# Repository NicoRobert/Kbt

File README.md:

# Keyboard Turbo

This is my first attempt of designing a split keyboard.
Mainly inspired by the [event0]( https://github.com/devplayer0/event0)

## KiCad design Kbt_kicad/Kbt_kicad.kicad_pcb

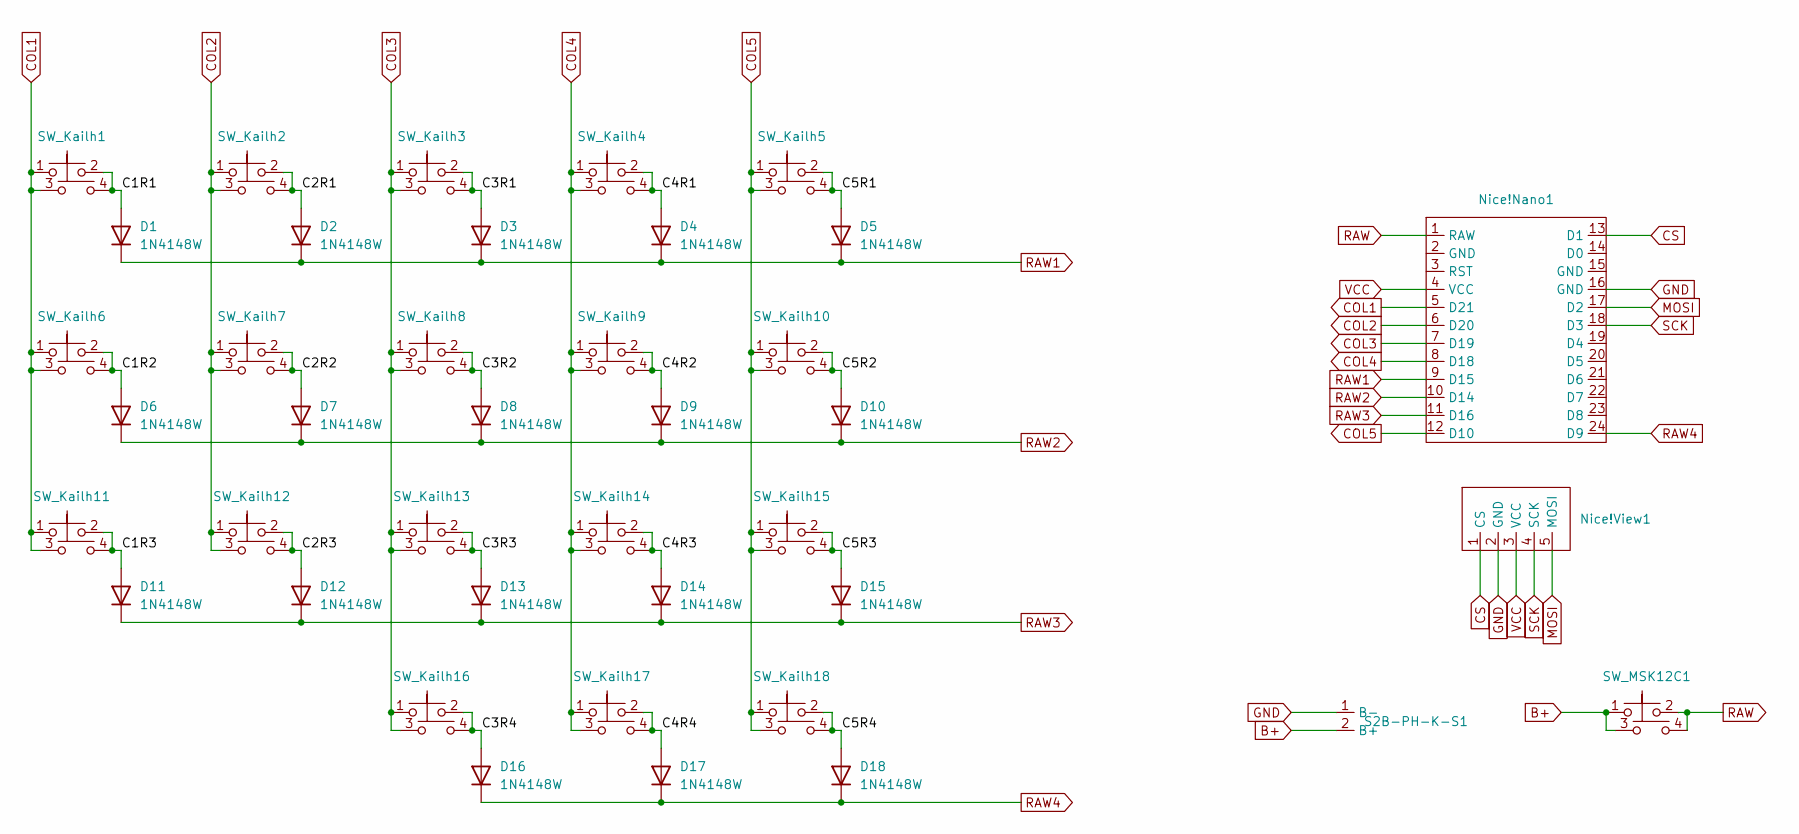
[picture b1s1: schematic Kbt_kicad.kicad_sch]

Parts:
D1, D2, D3, D4, D5, D6, D7, D8, D9, D10, D11, D12, D13, D14, D15, D16, D17, D18: 1N4148W; D_SOD-123-back
Nice!Nano1: Nice!Nano gpio
Nice!View1: Nice!View pins
S2B-PH-K-S1: S2B-PH-K-S
SW_Kailh1, SW_Kailh2, SW_Kailh3, SW_Kailh4, SW_Kailh5, SW_Kailh6, SW_Kailh7, SW_Kailh8, SW_Kailh9, SW_Kailh10, SW_Kailh11, SW_Kailh12, SW_Kailh13, SW_Kailh14, SW_Kailh15, SW_Kailh16, SW_Kailh17, SW_Kailh18: Kailh choc switch reversible
SW_MSK12C1: SW_MSK12C02

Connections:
/C1R1: D1.2 (A), SW_Kailh1.2, SW_Kailh1.4
/C1R2: D6.2 (A), SW_Kailh6.2, SW_Kailh6.4
/C1R3: D11.2 (A), SW_Kailh11.2, SW_Kailh11.4
/C2R1: D2.2 (A), SW_Kailh2.2, SW_Kailh2.4
/C2R2: D7.2 (A), SW_Kailh7.2, SW_Kailh7.4
/C2R3: D12.2 (A), SW_Kailh12.2, SW_Kailh12.4
/C3R1: D3.2 (A), SW_Kailh3.2, SW_Kailh3.4
/C3R2: D8.2 (A), SW_Kailh8.2, SW_Kailh8.4
/C3R3: D13.2 (A), SW_Kailh13.2, SW_Kailh13.4
/C3R4: D16.2 (A), SW_Kailh16.2, SW_Kailh16.4
/C4R1: D4.2 (A), SW_Kailh4.2, SW_Kailh4.4
/C4R2: D9.2 (A), SW_Kailh9.2, SW_Kailh9.4
/C4R3: D14.2 (A), SW_Kailh14.2, SW_Kailh14.4
/C4R4: D17.2 (A), SW_Kailh17.2, SW_Kailh17.4
/C5R1: D5.2 (A), SW_Kailh5.2, SW_Kailh5.4
/C5R2: D10.2 (A), SW_Kailh10.2, SW_Kailh10.4
/C5R3: D15.2 (A), SW_Kailh15.2, SW_Kailh15.4
/C5R4: D18.2 (A), SW_Kailh18.2, SW_Kailh18.4
B+: S2B-PH-K-S1.2 (B+), SW_MSK12C1.1, SW_MSK12C1.3
COL1: Nice!Nano1.5 (D21), SW_Kailh1.1, SW_Kailh1.3, SW_Kailh6.1, SW_Kailh6.3, SW_Kailh11.1, SW_Kailh11.3
COL2: Nice!Nano1.6 (D20), SW_Kailh2.1, SW_Kailh2.3, SW_Kailh7.1, SW_Kailh7.3, SW_Kailh12.1, SW_Kailh12.3
COL3: Nice!Nano1.7 (D19), SW_Kailh3.1, SW_Kailh3.3, SW_Kailh8.1, SW_Kailh8.3, SW_Kailh13.1, SW_Kailh13.3, SW_Kailh16.1, SW_Kailh16.3
COL4: Nice!Nano1.8 (D18), SW_Kailh4.1, SW_Kailh4.3, SW_Kailh9.1, SW_Kailh9.3, SW_Kailh14.1, SW_Kailh14.3, SW_Kailh17.1, SW_Kailh17.3
COL5: Nice!Nano1.12 (D10), SW_Kailh5.1, SW_Kailh5.3, SW_Kailh10.1, SW_Kailh10.3, SW_Kailh15.1, SW_Kailh15.3, SW_Kailh18.1, SW_Kailh18.3
CS: Nice!Nano1.13 (D1), Nice!View1.1 (CS)
GND: Nice!Nano1.16 (GND), Nice!View1.2 (GND), S2B-PH-K-S1.1 (B-)
MOSI: Nice!Nano1.17 (D2), Nice!View1.5 (MOSI)
RAW: Nice!Nano1.1 (RAW), SW_MSK12C1.2, SW_MSK12C1.4
RAW1: D1.1 (K), D2.1 (K), D3.1 (K), D4.1 (K), D5.1 (K), Nice!Nano1.9 (D15)
RAW2: D6.1 (K), D7.1 (K), D8.1 (K), D9.1 (K), D10.1 (K), Nice!Nano1.10 (D14)
RAW3: D11.1 (K), D12.1 (K), D13.1 (K), D14.1 (K), D15.1 (K), Nice!Nano1.11 (D16)
RAW4: D16.1 (K), D17.1 (K), D18.1 (K), Nice!Nano1.24 (D9)
SCK: Nice!Nano1.18 (D3), Nice!View1.4 (SCK)
VCC: Nice!Nano1.4 (VCC), Nice!View1.3 (VCC)

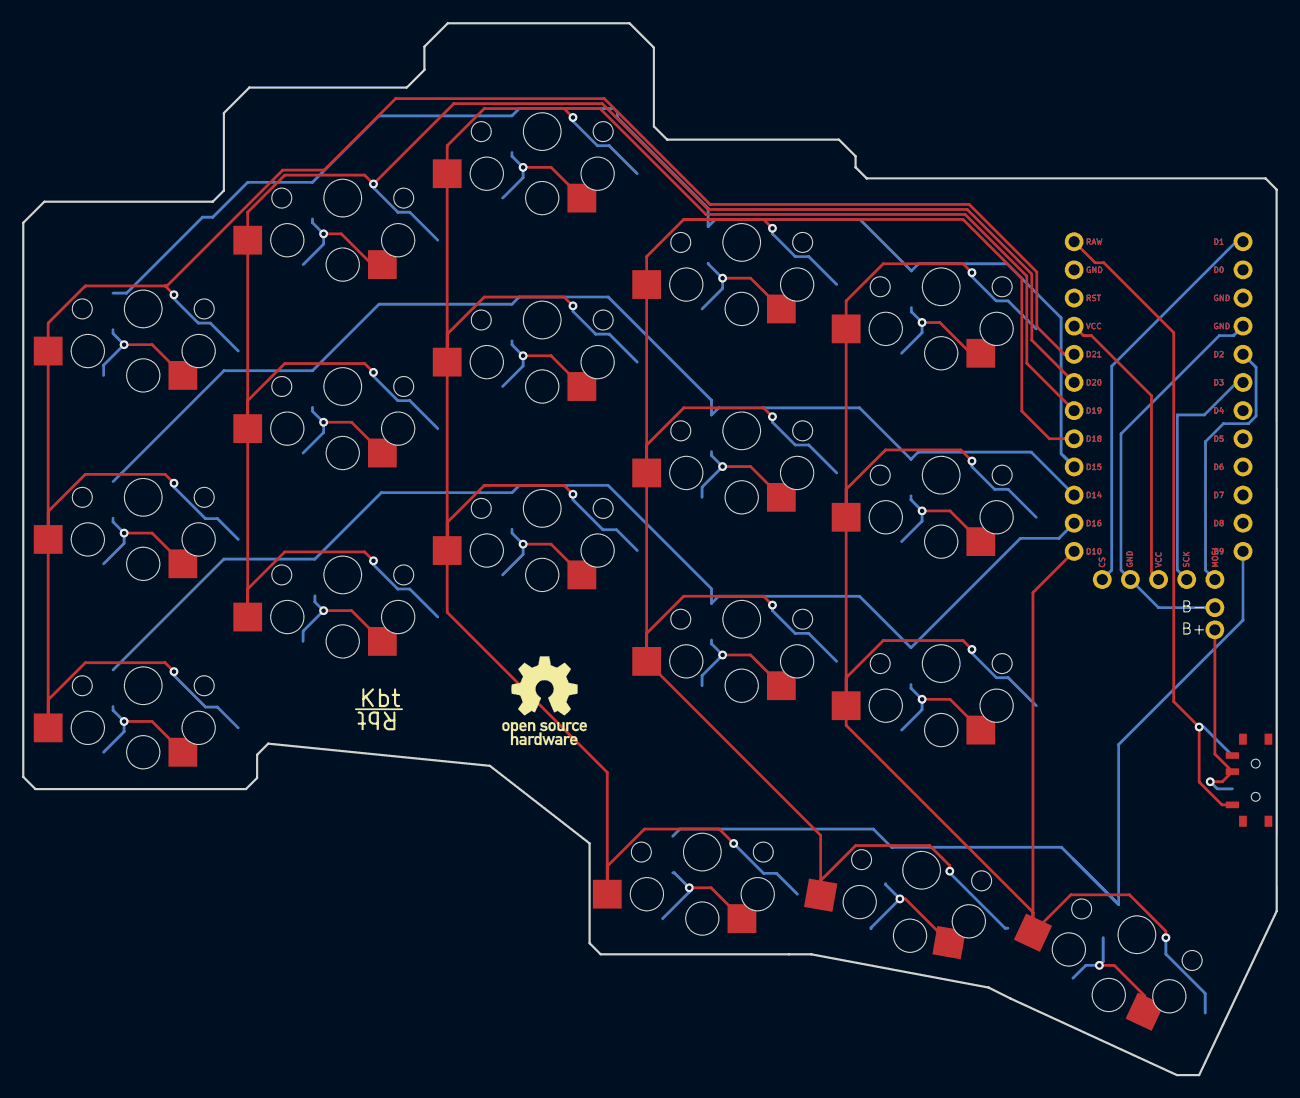
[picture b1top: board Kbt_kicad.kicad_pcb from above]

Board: 2 copper layers, 113.1 x 94.9 mm, 40 parts (0 on the bottom side), 34 nets.

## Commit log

2023-10-15 add: kicad project
2023-10-15 add: README
